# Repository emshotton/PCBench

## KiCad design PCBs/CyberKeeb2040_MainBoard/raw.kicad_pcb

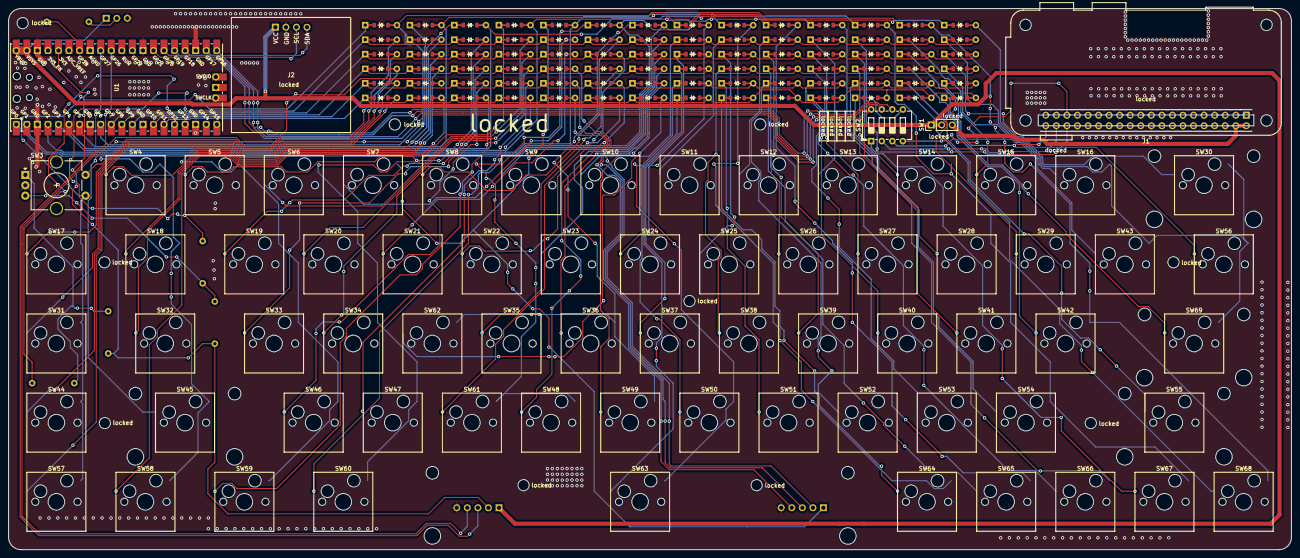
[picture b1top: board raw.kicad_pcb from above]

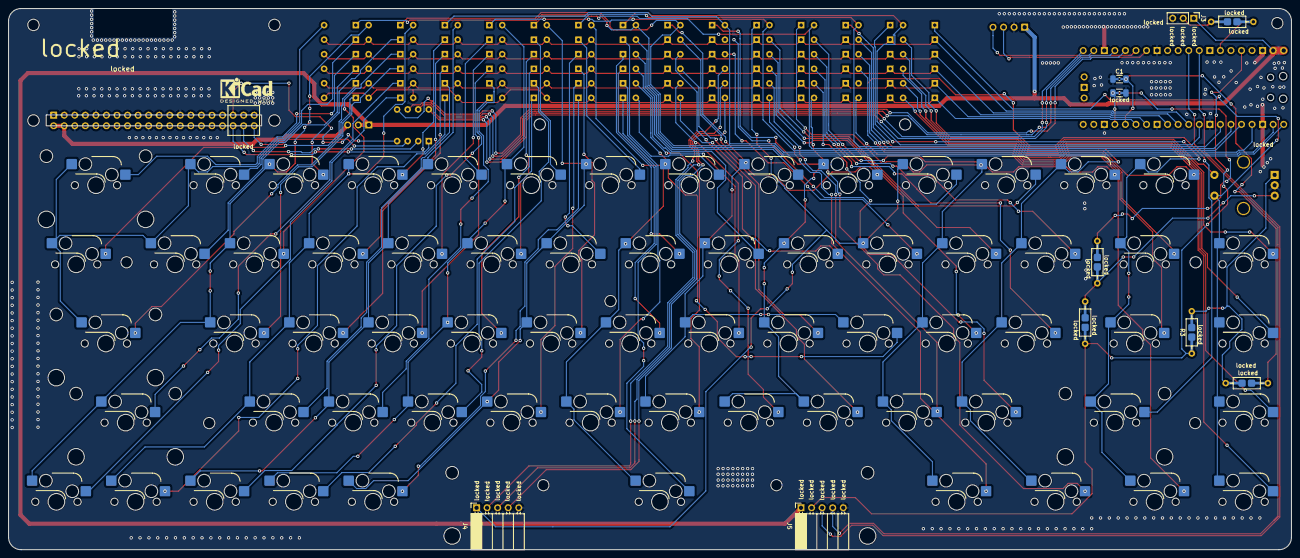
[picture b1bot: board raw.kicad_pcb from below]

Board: 2 copper layers, 308.8 x 130.2 mm, 166 parts (76 on the bottom side), 118 nets.

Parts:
C1: 0.01 μF; C_1206_3216Metric_Pad1.33x1.80mm_HandSolder
D1, D2, D3, D4, D5, D6, D7, D8, D9, D10, D11, D12, D13, D14, D15, D16, D17, D18, D19, D20, D21, D22, D23, D24, D25, D26, D27, D28, D29, D30, D31, D32, D33, D34, D35, D36, D37, D38, D39, D40, D41, D42, D43, D44, D45, D46, D47, D48, D49, D50, D51, D52, D53, D54, D55, D56, D57, D58, D59, D60, D61, D62, D63, D64, D65, D66, D67, D68, D69, D70, D71, D72, D73, D74, D75, D76, D77, D78, D79, D80, D81, D82, D83, D84: D; D_DO-35_SOD27_P7.62mm_Horizontal
J1: Pi_Zero; Raspberry_Pi_Zero_Socketed_THT_MountingHoles_Castellated
J2: JMD0.96C
J3: WS2812; PinHeader_1x03_P2.54mm_Vertical
J4: Extra_Keys; PinSocket_1x05_P2.54mm_Horizontal
J5: JoyStick_Or_I2C1; PinSocket_1x05_P2.54mm_Horizontal
R1: 330; R_Axial_DIN0207_L6.3mm_D2.5mm_P10.16mm_Horizontal_0603
R2, R3, R4, R5: 10k; R_Axial_DIN0207_L6.3mm_D2.5mm_P10.16mm_Horizontal_0402
SW1: PiPowerSwitch; PinHeader_1x03_P2.54mm_Vertical
SW2: SPI_SW; SW_DIP_SPSTx04_Slide_6.7x11.72mm_W7.62mm_P2.54mm_LowProfile
SW3: RotaryEncoder_Switch; RotaryEncoder_Alps_EC11E-Switch_Vertical_H20mm_CircularMoun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
SW4: SW_`; SW_Hotswap_Kailh_MX_1.00u
SW5: SW_1; SW_Hotswap_Kailh_MX_1.00u
SW6: SW_2; SW_Hotswap_Kailh_MX_1.00u
SW7: SW_3; SW_Hotswap_Kailh_MX_1.00u
SW8: SW_4; SW_Hotswap_Kailh_MX_1.00u
SW9: SW_5; SW_Hotswap_Kailh_MX_1.00u
SW10: SW_6; SW_Hotswap_Kailh_MX_1.00u
SW11: SW_7; SW_Hotswap_Kailh_MX_1.00u
SW12: SW_8; SW_Hotswap_Kailh_MX_1.00u
SW13: SW_9; SW_Hotswap_Kailh_MX_1.00u
SW14: SW_0; SW_Hotswap_Kailh_MX_1.00u
SW15: SW_-; SW_Hotswap_Kailh_MX_1.00u
SW16: SW_+; SW_Hotswap_Kailh_MX_1.00u
SW17: SW_esc; SW_Hotswap_Kailh_MX_1.00u
SW18: SW_tab; SW_Hotswap_Kailh_MX_1.50u
SW19: SW_q; SW_Hotswap_Kailh_MX_1.00u
SW20: SW_w; SW_Hotswap_Kailh_MX_1.00u
SW21: SW_e; SW_Hotswap_Kailh_MX_1.00u
SW22: SW_r; SW_Hotswap_Kailh_MX_1.00u
SW23: SW_t; SW_Hotswap_Kailh_MX_1.00u
SW24: SW_y; SW_Hotswap_Kailh_MX_1.00u
SW25: SW_u; SW_Hotswap_Kailh_MX_1.00u
SW26: SW_i; SW_Hotswap_Kailh_MX_1.00u
SW27: SW_o; SW_Hotswap_Kailh_MX_1.00u
SW28: SW_p; SW_Hotswap_Kailh_MX_1.00u
SW29: SW_[; SW_Hotswap_Kailh_MX_1.00u
SW30: SW_back; SW_Hotswap_Kailh_MX_2.00u
SW31: SW_del; SW_Hotswap_Kailh_MX_1.00u
SW32: SW_caps; SW_Hotswap_Kailh_MX_1.75u
SW33: SW_a; SW_Hotswap_Kailh_MX_1.00u
SW34: SW_s; SW_Hotswap_Kailh_MX_1.00u
SW35: SW_f; SW_Hotswap_Kailh_MX_1.00u
SW36: SW_g; SW_Hotswap_Kailh_MX_1.00u
SW37: SW_h; SW_Hotswap_Kailh_MX_1.00u
SW38: SW_j; SW_Hotswap_Kailh_MX_1.00u
SW39: SW_k; SW_Hotswap_Kailh_MX_1.00u
SW40: SW_l; SW_Hotswap_Kailh_MX_1.00u
SW41: SW_;; SW_Hotswap_Kailh_MX_1.00u
SW42: SW_'; SW_Hotswap_Kailh_MX_1.00u
SW43: SW_]; SW_Hotswap_Kailh_MX_1.00u
SW44: SW_ins; SW_Hotswap_Kailh_MX_1.00u
SW45: SW_shift; SW_Hotswap_Kailh_MX_2.25u
SW46: SW_z; SW_Hotswap_Kailh_MX_1.00u
SW47: SW_x; SW_Hotswap_Kailh_MX_1.00u
SW48: SW_v; SW_Hotswap_Kailh_MX_1.00u
SW49: SW_b; SW_Hotswap_Kailh_MX_1.00u
SW50: SW_n; SW_Hotswap_Kailh_MX_1.00u
SW51: SW_m; SW_Hotswap_Kailh_MX_1.00u
SW52: SW_,; SW_Hotswap_Kailh_MX_1.00u
SW53: SW_.; SW_Hotswap_Kailh_MX_1.00u
SW54: SW_/; SW_Hotswap_Kailh_MX_1.00u
SW55: SW_r_shift; SW_Hotswap_Kailh_MX_2.75u
SW56: SW_bkslash; SW_Hotswap_Kailh_MX_1.50u
SW57: SW_fn1; SW_Hotswap_Kailh_MX_1.00u
SW58: SW_ctrl; SW_Hotswap_Kailh_MX_1.25u
SW59: SW_super; SW_Hotswap_Kailh_MX_1.25u
SW60: SW_alt; SW_Hotswap_Kailh_MX_1.25u
SW61: SW_c; SW_Hotswap_Kailh_MX_1.00u
SW62: SW_d; SW_Hotswap_Kailh_MX_1.00u
SW63: SW_space; SW_Hotswap_Kailh_MX_6.25u
SW64: SW_fn2; SW_Hotswap_Kailh_MX_1.00u
SW65: SW_left; SW_Hotswap_Kailh_MX_1.00u
SW66: SW_down; SW_Hotswap_Kailh_MX_1.00u
SW67: SW_up; SW_Hotswap_Kailh_MX_1.00u
SW68: SW_right; SW_Hotswap_Kailh_MX_1.00u
SW69: SW_enter; SW_Hotswap_Kailh_MX_2.25u
U1: Pico; RPi_Pico_SMD_TH
locked: 0.01 μF; C_1206_3216Metric_Pad1.33x1.80mm_HandSolder

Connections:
+3V3: J5.2, R3.2, R4.1, U1.36 (3V3)
+5V: J2.1, J3.1, J5.1, SW1.1 (A), SW1.2 (B), U1.39 (VSYS), U1.40 (VBUS)
/Pi_VCC: J1.2, J1.4, SW1.3 (C)
ANG1: J5.3, U1.32 (GPIO27_ADC1)
ANG2: J5.4, U1.31 (GPIO26_ADC0)
C0: D1.2 (A), D8.1 (K), U1.9 (GPIO6)
C1: D2.2 (A), D9.1 (K), U1.7 (GPIO5)
C2: D3.2 (A), D10.1 (K), U1.6 (GPIO4)
C3: D4.2 (A), D11.1 (K), U1.5 (GPIO3)
C4: D5.2 (A), D12.1 (K), U1.4 (GPIO2)
C5: D6.2 (A), D13.1 (K), U1.2 (GPIO1)
C6: D7.2 (A), D14.1 (K), U1.1 (GPIO0)
Enc1: C1.2, R2.1, U1.16 (GPIO12)
Enc2: R5.2, U1.17 (GPIO13), locked.1
Encoder_SW_1: D15.2 (A), SW3.S2
Encoder_SW_2: D1.1 (K), SW3.S1, SW17.2 (B), SW31.2 (B), SW44.2 (B), SW57.2 (B)
Extra1: D47.2 (A), J4.2
Extra2: D61.2 (A), J4.3
Extra3: D75.2 (A), J4.4
ExtraSource: D5.1 (K), J4.1, SW7.2 (B), SW21.2 (B)
GND: C1.1, J1.6, J1.9, J1.14, J1.20, J1.25, J1.30, J1.34, J2.2, J3.3, J4.5, J5.5, SW3.C, U1.3 (GND), U1.8 (GND), U1.13 (GND), U1.18 (GND), U1.23 (GND), U1.28 (GND), U1.38 (GND), locked.2
I2C0_SCL: J2.3, U1.27 (GPIO21)
I2C0_SDA: J2.4, U1.26 (GPIO20)
LED: R1.1, U1.34 (GPIO28_ADC2)
unnamed: D2.1 (K), SW4.2 (B), SW18.2 (B), SW32.2 (B), SW45.2 (B), SW58.2 (B)
unnamed: D3.1 (K), SW5.2 (B), SW19.2 (B), SW33.2 (B), SW46.2 (B), SW59.2 (B)
unnamed: D4.1 (K), SW6.2 (B), SW20.2 (B), SW34.2 (B), SW47.2 (B), SW60.2 (B)
unnamed: D6.1 (K), SW8.2 (B), SW22.2 (B), SW35.2 (B), SW48.2 (B), SW61.2 (B)
unnamed: D7.1 (K), SW9.2 (B), SW23.2 (B), SW36.2 (B), SW49.2 (B), SW62.2 (B)
unnamed: D8.2 (A), SW10.2 (B), SW24.2 (B), SW37.2 (B), SW50.2 (B), SW63.2 (B)
unnamed: D9.2 (A), SW11.2 (B), SW25.2 (B), SW38.2 (B), SW51.2 (B), SW64.2 (B)
unnamed: D10.2 (A), SW12.2 (B), SW26.2 (B), SW39.2 (B), SW52.2 (B), SW65.2 (B)
unnamed: D11.2 (A), SW13.2 (B), SW27.2 (B), SW40.2 (B), SW53.2 (B), SW66.2 (B)
unnamed: D12.2 (A), SW14.2 (B), SW28.2 (B), SW41.2 (B), SW54.2 (B), SW67.2 (B)
unnamed: D13.2 (A), SW15.2 (B), SW29.2 (B), SW42.2 (B), SW55.2 (B), SW68.2 (B)
unnamed: D14.2 (A), SW16.2 (B), SW30.2 (B), SW43.2 (B), SW56.2 (B), SW69.2 (B)
unnamed: D16.2 (A), SW4.1 (A)
unnamed: D17.2 (A), SW5.1 (A)
unnamed: D18.2 (A), SW6.1 (A)
unnamed: D19.2 (A), SW7.1 (A)
unnamed: D20.2 (A), SW8.1 (A)
unnamed: D21.2 (A), SW9.1 (A)
unnamed: D22.1 (K), SW10.1 (A)
unnamed: D23.1 (K), SW11.1 (A)
unnamed: D24.1 (K), SW12.1 (A)
unnamed: D25.1 (K), SW13.1 (A)
unnamed: D26.1 (K), SW14.1 (A)
unnamed: D27.1 (K), SW15.1 (A)
unnamed: D28.1 (K), SW16.1 (A)
unnamed: D29.2 (A), SW17.1 (A)
unnamed: D30.2 (A), SW18.1 (A)
unnamed: D31.2 (A), SW19.1 (A)
unnamed: D32.2 (A), SW20.1 (A)
unnamed: D33.2 (A), SW21.1 (A)
unnamed: D34.2 (A), SW22.1 (A)
unnamed: D35.2 (A), SW23.1 (A)
unnamed: D36.1 (K), SW24.1 (A)
unnamed: D37.1 (K), SW25.1 (A)
unnamed: D38.1 (K), SW26.1 (A)
unnamed: D39.1 (K), SW27.1 (A)
unnamed: D40.1 (K), SW28.1 (A)
unnamed: D41.1 (K), SW29.1 (A)
unnamed: D42.1 (K), SW30.1 (A)
unnamed: D43.2 (A), SW31.1 (A)
unnamed: D44.2 (A), SW32.1 (A)
unnamed: D45.2 (A), SW33.1 (A)
unnamed: D46.2 (A), SW34.1 (A)
unnamed: D48.2 (A), SW35.1 (A)
unnamed: D49.2 (A), SW36.1 (A)
unnamed: D50.1 (K), SW37.1 (A)
unnamed: D51.1 (K), SW38.1 (A)
unnamed: D52.1 (K), SW39.1 (A)
unnamed: D53.1 (K), SW40.1 (A)
unnamed: D54.1 (K), SW41.1 (A)
unnamed: D55.1 (K), SW42.1 (A)
unnamed: D56.1 (K), SW43.1 (A)
unnamed: D57.2 (A), SW44.1 (A)
unnamed: D58.2 (A), SW45.1 (A)
unnamed: D59.2 (A), SW46.1 (A)
unnamed: D60.2 (A), SW47.1 (A)
unnamed: D62.2 (A), SW48.1 (A)
unnamed: D63.2 (A), SW49.1 (A)
unnamed: D64.1 (K), SW50.1 (A)
unnamed: D65.1 (K), SW51.1 (A)
unnamed: D66.1 (K), SW52.1 (A)
unnamed: D67.1 (K), SW53.1 (A)
unnamed: D68.1 (K), SW54.1 (A)
unnamed: D69.1 (K), SW55.1 (A)
unnamed: D70.1 (K), SW56.1 (A)
unnamed: D71.2 (A), SW57.1 (A)
unnamed: D72.2 (A), SW58.1 (A)
unnamed: D73.2 (A), SW59.1 (A)
unnamed: D74.2 (A), SW60.1 (A)
unnamed: D76.2 (A), SW61.1 (A)
unnamed: D77.2 (A), SW62.1 (A)
unnamed: D78.1 (K), SW63.1 (A)
unnamed: D79.1 (K), SW64.1 (A)
unnamed: D80.1 (K), SW65.1 (A)
unnamed: D81.1 (K), SW66.1 (A)
unnamed: D82.1 (K), SW67.1 (A)
unnamed: D83.1 (K), SW68.1 (A)
unnamed: D84.1 (K), SW69.1 (A)
unnamed: J3.2, R1.2
unnamed: R2.2, R3.1, SW3.A
unnamed: R4.2, R5.1, SW3.B
PI_SPI_CS: J1.36, SW2.1
PI_SPI_MISO: J1.35, SW2.4
PI_SPI_MOSI: J1.38, SW2.2
PI_SPI_SCK: J1.40, SW2.3
R0: D15.1 (K), D16.1 (K), D17.1 (K), D18.1 (K), D19.1 (K), D20.1 (K), D21.1 (K), D22.2 (A), D23.2 (A), D24.2 (A), D25.2 (A), D26.2 (A), D27.2 (A), D28.2 (A), U1.10 (GPIO7)
R1: D29.1 (K), D30.1 (K), D31.1 (K), D32.1 (K), D33.1 (K), D34.1 (K), D35.1 (K), D36.2 (A), D37.2 (A), D38.2 (A), D39.2 (A), D40.2 (A), D41.2 (A), D42.2 (A), U1.11 (GPIO8)
R2: D43.1 (K), D44.1 (K), D45.1 (K), D46.1 (K), D47.1 (K), D48.1 (K), D49.1 (K), D50.2 (A), D51.2 (A), D52.2 (A), D53.2 (A), D54.2 (A), D55.2 (A), D56.2 (A), U1.12 (GPIO9)
R3: D57.1 (K), D58.1 (K), D59.1 (K), D60.1 (K), D61.1 (K), D62.1 (K), D63.1 (K), D64.2 (A), D65.2 (A), D66.2 (A), D67.2 (A), D68.2 (A), D69.2 (A), D70.2 (A), U1.14 (GPIO10)
R4: D71.1 (K), D72.1 (K), D73.1 (K), D74.1 (K), D75.1 (K), D76.1 (K), D77.1 (K), D78.2 (A), D79.2 (A), D80.2 (A), D81.2 (A), D82.2 (A), D83.2 (A), D84.2 (A), U1.15 (GPIO11)
SPI_CS: SW2.8, U1.22 (GPIO17)
SPI_MISO: SW2.5, U1.25 (GPIO19)
SPI_MOSI: SW2.7, U1.21 (GPIO16)
SPI_SCK: SW2.6, U1.24 (GPIO18)

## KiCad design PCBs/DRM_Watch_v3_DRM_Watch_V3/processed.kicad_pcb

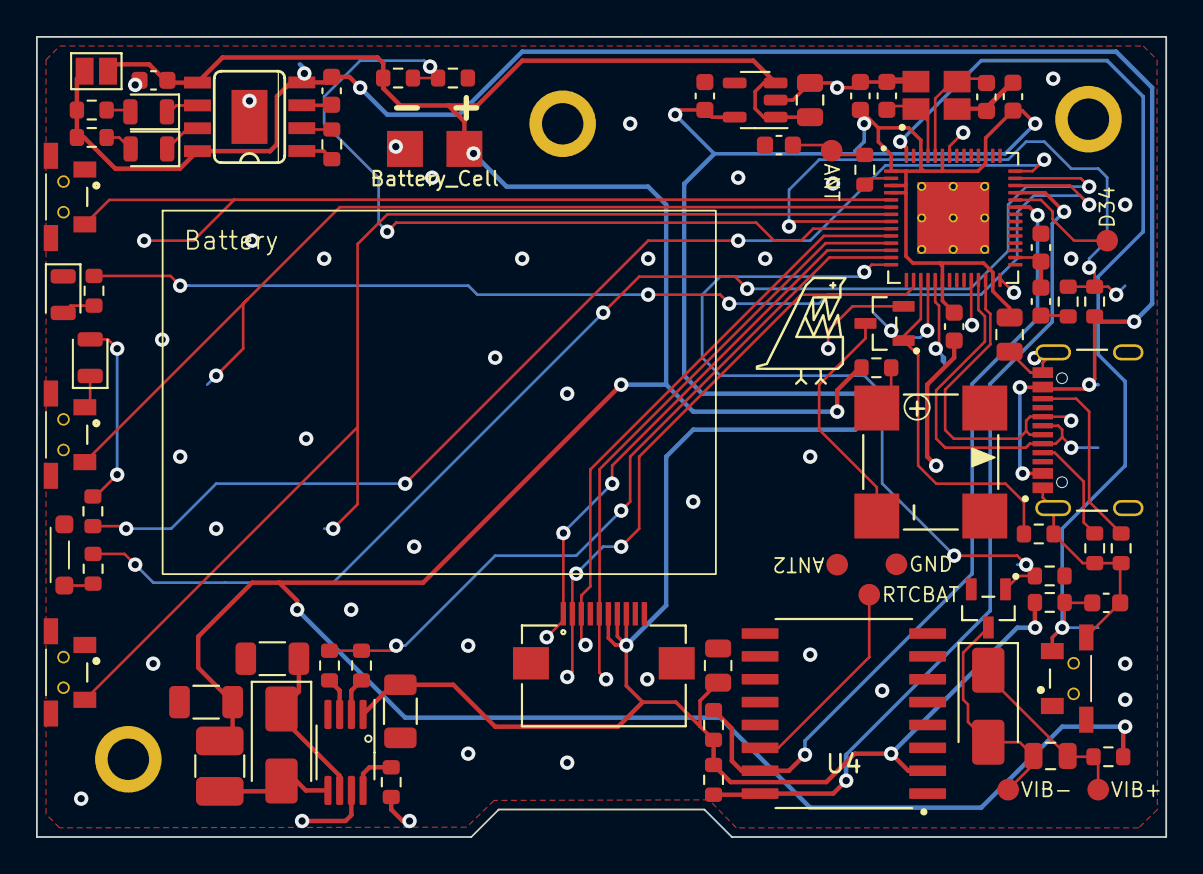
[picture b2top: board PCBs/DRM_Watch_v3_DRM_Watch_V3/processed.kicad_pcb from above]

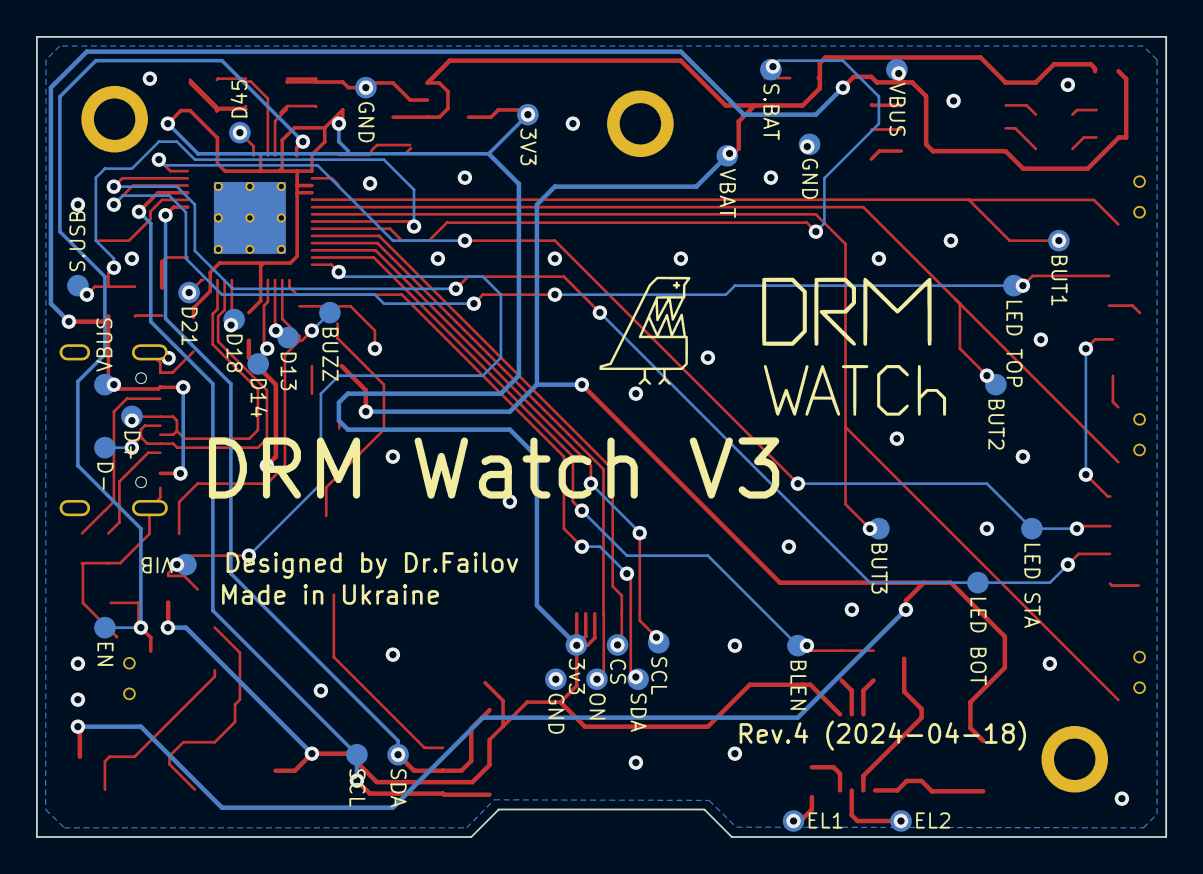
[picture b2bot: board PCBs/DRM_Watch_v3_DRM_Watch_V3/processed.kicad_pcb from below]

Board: 2 copper layers, 62.7 x 44.4 mm, 112 parts (35 on the bottom side), 57 nets.

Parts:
BT1: Battery_Cell; Battery
C1: 0.1uF; C_0805_2012Metric
C2, C3, C13: 10pF; C_0603_1608Metric
C4, C5, C6, C8: 0.1uF; C_0603_1608Metric
C7, C14: 1uF; C_0603_1608Metric
C9, C10, C19: 1uF; C_0805_2012Metric
C11, C12, C15: 10uF; C_0603_1608Metric
C16: 12nF 200V; C_1206
C17: 4.7uF; C_1206
C18: 0.1uF; C_1206
D1, D4: LED RED; HOLE_LED_0805_2012Metric
D2: 020 SMD Side View LED White 6000K; SMD-LED-Side-View
D3, D5: LED BLUE; HOLE_LED_0805_2012Metric
D6, D7: US1D
J1: TYPE-C-31-M-12; HRO_TYPE-C-31-M-12
J2: FPC 10pin 0.5mm pitch; 687110149022
JP1: Connect this to directly power VCC from USB; SolderJumper-2_P1.3mm_Open_Pad1.0x1.5mm
L1: 220uH; Inductor-L_1210_3225Metric
LS1: CMT-7525S-SMT; CUI_CMT-7525S-SMT
M1, M2, M3: Brass SMTSO-M1.4X3X1.5-2X0.8; m1.4-screw-mount
Q1, Q2: 2N7002LT1G (SOT-23-3); SOT95P240X111-3N
R1, R7, R8, R22: 1K; R_0603_1608Metric
R2, R3: 5.1K; R_0603_1608Metric
R4, R5, R6, R10, R23: R22; R_0603_1608Metric
R9: 2K; R_0603_1608Metric
R11, R12, R13, R14: 100K; R_0603_1608Metric
R15: 0 ohm; R_0603_1608Metric
R16: 10K; R_0603_1608Metric
R17: 560K; R_0603_1608Metric
R18: 2M; R_0603_1608Metric
R19, R20: 4.3K; R_0603_1608Metric
R21: 500R; R_0603_1608Metric
S1, S2, S3, S4: 2*4*3.5mm Micro SMD Tact Switch Side Button; SW_TL3330AF130QG
TP1: 3V3; TestPoint_Pad
TP2: VBAT; TestPoint_Pad
TP3: BUT1; TestPoint_Pad
TP4: BUT2; TestPoint_Pad
TP5: BUT3; TestPoint_Pad
TP6, TP8, TP9, TP17: GND; TestPoint_Pad
TP7, TP23: VBUS; TestPoint_Pad
TP10: EN; TestPoint_Pad
TP11: S.BAT; TestPoint_Pad
TP12: S.USB; TestPoint_Pad
TP13, TP30: SCL; TestPoint_Pad
TP14, TP29: SDA; TestPoint_Pad
TP15: CS; TestPoint_Pad
TP16: ON; TestPoint_Pad
TP18: 3v3; TestPoint_Pad
TP19: LED TOP; TestPoint_Pad
TP20: LED BOT; TestPoint_Pad
TP21: LED STA; TestPoint_Pad
TP22: BUZZ; TestPoint_Pad
TP24: D+; TestPoint_Pad
TP25: D-; TestPoint_Pad
TP26: EL1; TestPoint_Pad
TP27: ANT; TestPoint_Pad
TP28: ANT2; TestPoint_Pad
TP31: D14; TestPoint_Pad
TP32: EL2; TestPoint_Pad
TP33: D18; TestPoint_Pad
TP34: D21; TestPoint_Pad
TP35: D45; TestPoint_Pad
TP36: D34; TestPoint_Pad
TP37: D13; TestPoint_Pad
TP38: BLEN; TestPoint_Pad
TP39: RTCBAT; TestPoint_Pad
TP40: VIB+; TestPoint_Pad
TP41: VIB-; TestPoint_Pad
TP42: VIB; TestPoint_Pad
U1: ESP32-S2FN4R2; QFN-56-1EP_7x7mm_P0.4mm_EP4x4mm_ThermalVias
U2: ME6211 SOT23-5 3.3V; ME6211 SOT-23-5
U3: TP4056; SO08
U4: DS3231S; SOIC127P1032X265-16N
U5: Microchip HV857; HV857
Y1: 3225 4PIN 40Mhz 3.2*2.5mm Passive SMD Quartz Reso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; Oscilator

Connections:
+3V3: C1.2, C4.1, C5.1, C6.1, C10.1, C15.2, C18.1, J2.6 (VDDA), J2.7 (VDD), J2.8 (EXTMODE), R16.1, R19.2, R20.2, TP1.1, TP18.1, U1.1 (VDDA), U1.3 (VDD3P3), U1.4 (VDD3P3), U1.20 (VDD3P3_RTC), U1.27 (VDD3P3_RTC_IO), U1.45 (VDD3P3_CPU), U1.51 (VDDA), U1.54 (VDDA), U2.5 (V_out), U4.2 (VCC), U5.1 (VDD)
GND: BT1.2 (-), C1.1, C2.1, C3.2, C4.2, C5.2, C6.2, C7.2, C8.2, C9.2, C10.2, C11.2, C12.1, C13.1, C14.1, C15.1, C16.2, C17.2, C18.2, D1.1 (K), D2.1 (K), D5.1 (K), J1.A1_B12 (GND), J1.B1_A12 (GND), J1.S1 (SHIELD), J1.S2 (SHIELD), J1.S3 (SHIELD), J1.S4 (SHIELD), J2.9 (GND), J2.10 (GNDA), J2.Z1 (Mount), J2.Z2 (Mount), M1.1, M2.1, M3.1, Q1.2, Q2.2, R1.2, R2.2, R3.1, R9.2, R12.2, R14.2, R22.2, S1.1, S1.3 (Shield), S2.1, S2.3 (Shield), S3.1, S3.3 (Shield), S4.1, S4.3 (Shield), TP6.1, TP8.1, TP9.1, TP17.1, U1.57 (GND), U2.2 (GND), U3.1 (TEMP), U3.3 (GND), U3.9 (HEAT), U4.5 (N.C.), U4.6 (N.C.), U4.7 (N.C.), U4.8 (N.C.), U4.9 (N.C.), U4.10 (N.C.), U4.11 (N.C.), U4.12 (N.C.), U4.13 (GND), U5.4 (GND), Y1.2 (GND), Y1.4 (GND)
unnamed: C13.2, R15.1, TP27.1
unnamed: D1.2 (A), R5.1
unnamed: D2.2 (A), R6.1
unnamed: D3.2 (A), R7.2
unnamed: D3.1 (K), U3.6 (STDBY)
unnamed: D4.2 (A), R8.2
unnamed: D4.1 (K), U3.7 (CHRGE)
unnamed: D5.2 (A), R10.1
unnamed: D6.2 (A), L1.1, U5.5 (LX)
unnamed: C16.1, D6.1 (K), U5.6 (CS)
unnamed: C19.1, D7.2 (A), Q2.3, TP41.1
unnamed: C19.2, D7.1 (K), R23.1, TP40.1
unnamed: J1.A5 (CC1), R3.2
unnamed: J1.B5 (CC2), R2.1
unnamed: J1.A7 (DN1), J1.B7 (DN2), TP25.1, U1.25 (GPIO19/ADC2_CH8/USB_D-)
unnamed: J1.A6 (DP1), J1.B6 (DP2), TP24.1, U1.26 (GPIO20/ADC2_CH9/USB_D+)
unnamed: J2.3 (CS), TP15.1, U1.10 (GPIO5/ADC1_CH4)
unnamed: J2.5 (ON\OFF), TP16.1, U1.11 (GPIO6/ADC1_CH5)
unnamed: J2.1 (SCL), TP13.1, U1.12 (GPIO7/ADC1_CH6)
unnamed: J2.2 (SDA), TP14.1, U1.16 (GPIO11/ADC2_CH0)
unnamed: LS1.N, Q1.3
unnamed: LS1.P, R4.1
unnamed: R21.1, TP26.1
unnamed: C14.2, R16.2, S3.2, TP10.1, U1.56 (CHIP_PU/RESET)
unnamed: S1.2, TP3.1, U1.5 (GPIO0/BOOT)
unnamed: S2.2, TP4.1, U1.6 (GPIO1/ADC1_CH0)
unnamed: S4.2, TP5.1, U1.7 (GPIO2/ADC1_CH1)
unnamed: R13.2, R14.1, TP12.1, U1.8 (GPIO3/ADC1_CH2)
unnamed: R11.2, R12.1, TP11.1, U1.9 (GPIO4/ADC1_CH3)
unnamed: R17.1, R18.1, TP38.1, U1.13 (GPIO8/ADC1_CH7)
unnamed: Q2.1, R22.1, TP42.1, U1.14 (GPIO9/ADC1_CH8)
unnamed: Q1.1, R1.1, TP22.1, U1.17 (GPIO12/ADC2_CH1)
unnamed: TP37.1, U1.18 (GPIO13/ADC2_CH2)
unnamed: TP31.1, U1.19 (GPIO14/ADC2_CH3)
unnamed: TP33.1, U1.24 (GPIO18/ADC2_CH7/DAC_2)
unnamed: TP34.1, U1.28 (GPIO21)
unnamed: R19.1, TP29.1, U1.37 (GPIO33), U4.15 (SDA)
unnamed: TP36.1, U1.38 (GPIO34)
unnamed: R20.1, TP30.1, U1.39 (GPIO35), U4.16 (SCL)
unnamed: R5.2, TP19.1, U1.40 (GPIO36)
unnamed: R6.2, TP20.1, U1.41 (GPIO37)
unnamed: R10.2, TP21.1, U1.42 (GPIO38)
unnamed: TP35.1, U1.50 (GPIO45)
unnamed: R15.2, U1.2 (LNA_IN/RF)
unnamed: C7.1, C8.1, U1.30 (VDD_SPI)
unnamed: C3.1, U1.52 (XTAL_N), Y1.3 (XTAL_N)
unnamed: C2.2, U1.53 (XTAL_P), Y1.1 (XTAL_P)
unnamed: R9.1, U3.2 (PROG)
unnamed: TP39.1, U4.14 (VBAT)
unnamed: R18.2, U5.3 (REL-Osc)
unnamed: R17.2, U5.2 (RSW-Osc)
unnamed: R21.2, U5.8 (VA)
unnamed: TP32.1, U5.7 (VB)
VBUS: C12.2, J1.A4_B9 (VBUS), J1.B4_A9 (VBUS), JP1.1 (A), R7.1, R8.1, R13.1, TP7.1, TP23.1, U3.4 (VCC), U3.8 (CE)
VCC: BT1.1 (+), C9.1, C11.1, C17.1, JP1.2 (B), L1.2, R4.2, R11.1, R23.2, TP2.1, U2.1 (V_in), U2.3 (CE), U3.5 (BAT)

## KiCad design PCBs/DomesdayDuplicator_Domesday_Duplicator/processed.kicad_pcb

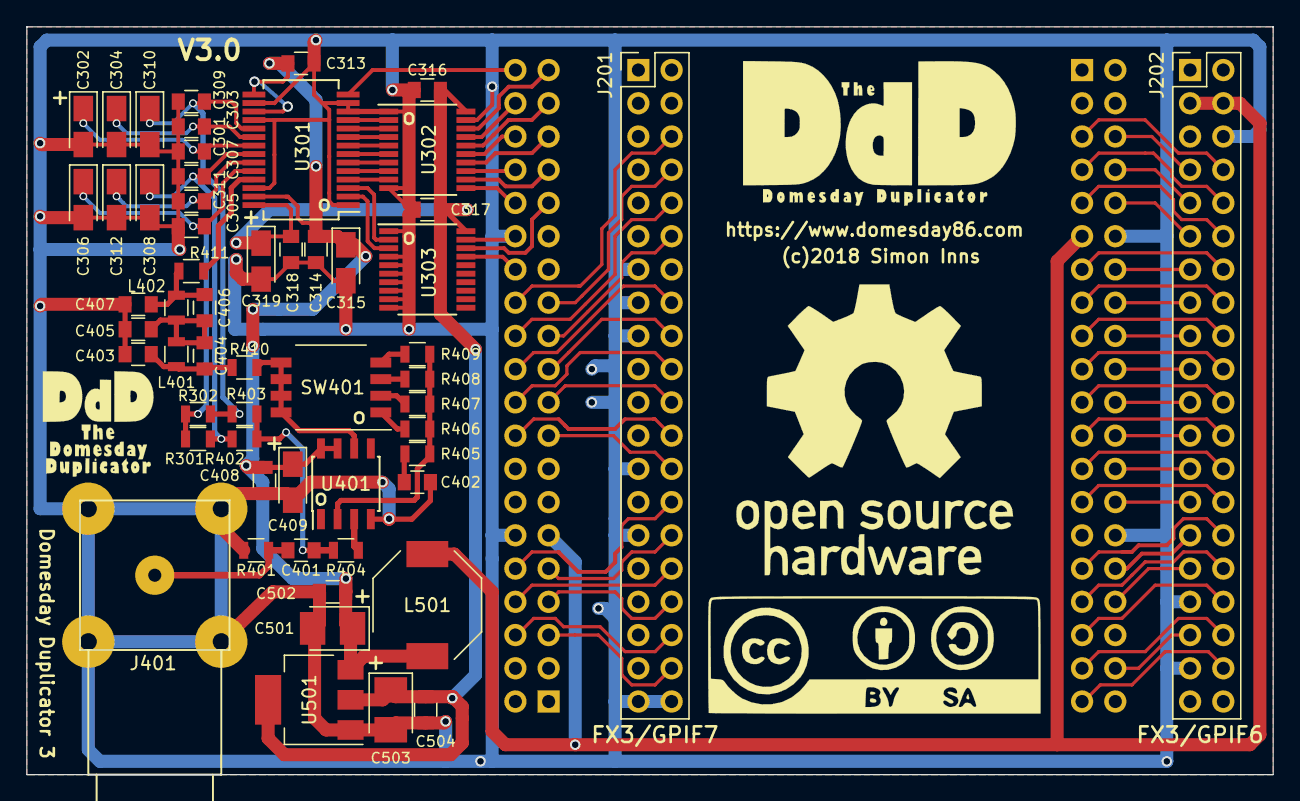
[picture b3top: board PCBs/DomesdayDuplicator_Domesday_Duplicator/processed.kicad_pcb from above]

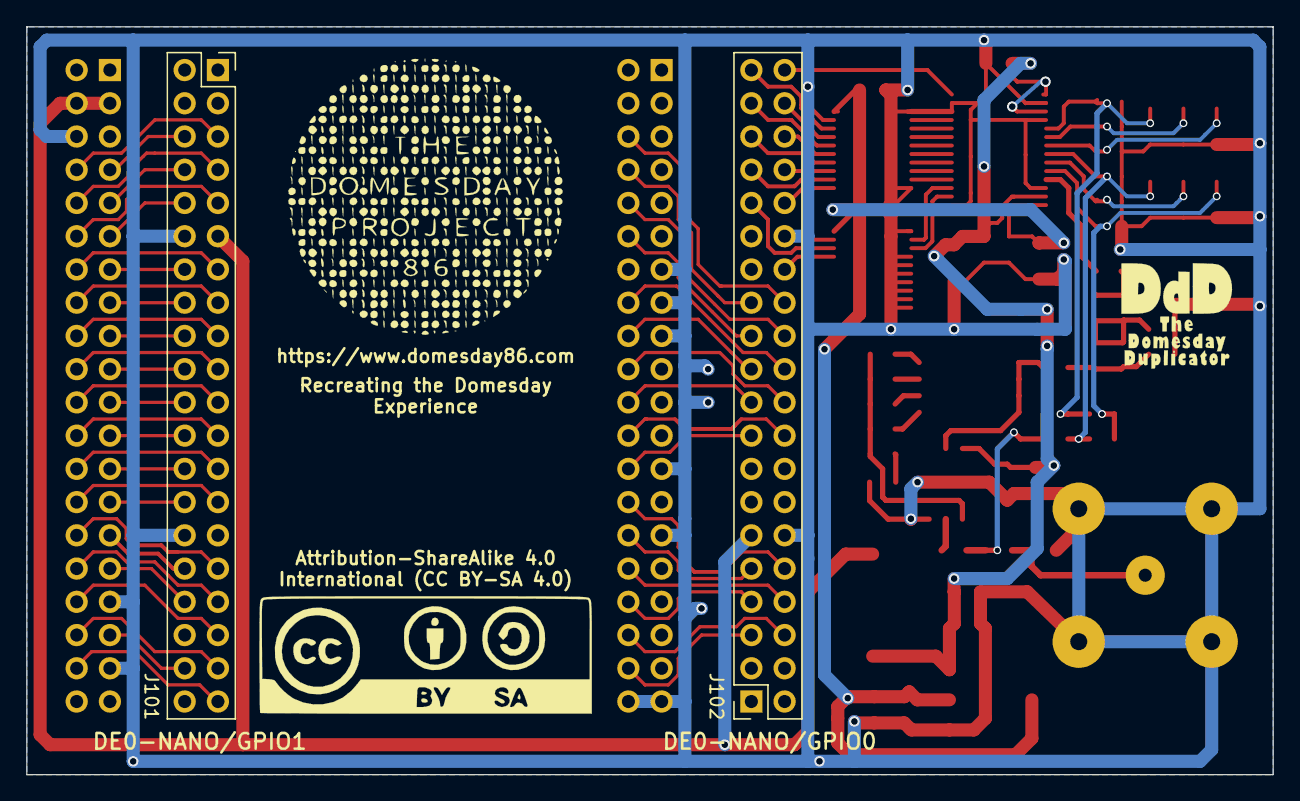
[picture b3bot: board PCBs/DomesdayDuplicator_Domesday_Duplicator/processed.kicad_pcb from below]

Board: 2 copper layers, 95.2 x 57.2 mm, 59 parts (2 on the bottom side), 91 nets.

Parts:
C301, C303, C305, C307, C309, C311, C313, C314, C316, C317, C318, C401, C402, C408, C502, C504: 100nF; C_0805
C302, C304, C306, C308, C310, C312, C315, C319, C409: 2.2uF Tant; CP_Tantalum_Case-A_EIA-3216-18_Reflow
C403: 330pF; C_0805
C404: 33pF; C_0805
C405: 470pF; C_0805
C406: 100pF; C_0805
C407: 270pF; C_0805
C501, C503: 10uF TANT; CP_Tantalum_Case-B_EIA-3528-21_Reflow
J101: DE0-Nano_GPIO1; Socket_Strip_Straight_2x20_Pitch2.54mm
J102: DE0-Nano_GPIO0; Socket_Strip_Straight_2x20_Pitch2.54mm
J201: GPIFII_J7; Pin_Header_Straight_2x20_Pitch2.54mm
J202: GPIFII_J6; Pin_Header_Straight_2x20_Pitch2.54mm
J401: BNC_Rosenberger; BNC Socket
L401: 680nH; L_0805
L402: 560nH; L_0805
L501: 100uH; Inductor_Bourns-SRU8043
R301, R402, R403, R407: 1K; R_0805
R302: 1K2; R_0805
R401: 56R; R_0805
R404: 100R; R_0805
R405: 200R; R_0805
R406: 1K5; R_0805
R408: 680R; R_0805
R409: 560R; R_0805
R410, R411: 47R; R_0805
SW401: Gain Select; SW_DIP_x4_W7.62mm_Slide_Copal_CHS-B
U301: ADS825; SSOP-28_5.3x10.2mm_Pitch0.65mm
U302, U303: 74LVTH541_PWR; TSSOP-20_4.4x6.5mm_Pitch0.65mm
U401: OPA690; SOIC-8_3.9x4.9mm_Pitch1.27mm
U501: LM1117-3.3; SOT-223-3_TabPin2

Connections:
+3.3VA: C316.1, C317.1, C318.1, C319.1, C503.1, C504.1, U301.28, U302.20, U303.20, U501.2
+5V: J101.11, J102.11, J202.3, J202.4, L501.2
+5VA: C313.1, C314.1, C315.1, C408.1, C409.1, C501.1, C502.1, L501.1, U301.15, U301.17, U301.27, U401.7, U401.8, U501.3
/ADC/IN: R411.2, U301.25
/ADC/REFB: C309.1, C310.1, R302.1, R403.1, U301.19
/ADC/REFT: C307.1, C308.1, R301.2, R402.2, U301.22
ADC_CLK: J102.40, U301.14
ADC_DATA0: J102.39, U302.18
ADC_DATA1: J102.38, U302.17
ADC_DATA2: J102.37, U302.16
ADC_DATA3: J102.36, U302.15
ADC_DATA4: J102.35, U302.14
ADC_DATA5: J102.34, U302.13
ADC_DATA6: J102.33, U302.12
ADC_DATA7: J102.32, U302.11
ADC_DATA8: J102.31, U303.18
ADC_DATA9: J102.28, U303.17
GND: C301.2, C302.2, C303.2, C304.2, C305.2, C306.2, C307.2, C308.2, C309.2, C310.2, C311.2, C312.2, C313.2, C314.2, C315.2, C316.2, C317.2, C318.2, C319.2, C402.2, C403.2, C405.2, C407.2, C408.2, C409.2, C501.2, C502.2, C503.2, C504.2, J101.12, J101.30, J102.12, J102.30, J201.13, J201.15, J201.17, J201.25, J201.29, J201.39, J201.40, J202.6, J202.33, J202.37, J401.2, J401.3, J401.4, J401.5, R401.1, U301.1, U301.12, U301.13, U301.16, U301.18, U301.26, U302.1, U302.10, U302.19, U303.1, U303.4, U303.5, U303.6, U303.7, U303.8, U303.9, U303.10, U303.19, U401.4, U501.1
unnamed: C301.1, C302.1, U301.21
unnamed: C303.1, C304.1, U301.20
unnamed: C305.1, C306.1, R301.1, R302.2, U301.24
unnamed: C311.1, C312.1, U301.23
unnamed: C401.1, R402.1, R403.2, R404.1
unnamed: C401.2, J401.1, R401.2
unnamed: C402.1, R405.1
unnamed: C403.1, C404.1, L401.2, R410.2
unnamed: C404.2, C405.1, C406.1, L401.1, L402.2
unnamed: C406.2, C407.1, L402.1, R411.1
unnamed: R404.2, U401.3
unnamed: R405.2, R406.1, R407.1, R408.1, R409.1, U401.2
unnamed: R406.2, SW401.1
unnamed: R407.2, SW401.2
unnamed: R408.2, SW401.3
unnamed: R409.2, SW401.4
unnamed: R410.1, SW401.5, SW401.6, SW401.7, SW401.8, U401.6
unnamed: U301.2, U303.3
unnamed: U301.3, U303.2
unnamed: U301.4, U302.9
unnamed: U301.5, U302.8
unnamed: U301.6, U302.7
unnamed: U301.7, U302.6
unnamed: U301.8, U302.5
unnamed: U301.9, U302.4
unnamed: U301.10, U302.3
unnamed: U301.11, U302.2
USB_CTL0: J101.34, J202.31
USB_CTL1: J101.32, J202.29
USB_CTL2: J101.28, J202.27
USB_CTL3: J101.26, J202.25
USB_CTL4: J101.24, J202.23
USB_CTL5: J101.22, J202.21
USB_CTL6: J101.20, J202.19
USB_CTL7: J101.18, J202.17
USB_CTL8: J101.16, J202.15
USB_CTL9: J101.14, J202.13
USB_CTL10: J101.10, J202.11
USB_CTL11: J101.8, J202.9
USB_CTL12: J101.6, J202.7
USB_DATA0: J101.39, J202.38
USB_DATA1: J101.37, J202.36
USB_DATA2: J101.35, J202.34
USB_DATA3: J101.33, J202.32
USB_DATA4: J101.31, J202.30
USB_DATA5: J101.27, J202.28
USB_DATA6: J101.25, J202.26
USB_DATA7: J101.23, J202.24
USB_DATA8: J101.21, J202.22
USB_DATA9: J101.19, J202.20
USB_DATA10: J101.17, J202.18
USB_DATA11: J101.15, J202.16
USB_DATA12: J101.13, J202.14
USB_DATA13: J101.9, J202.12
USB_DATA14: J101.7, J202.10
USB_DATA15: J101.5, J202.8
USB_DATA16: J102.5, J201.38
USB_DATA17: J102.6, J201.36
USB_DATA18: J102.7, J201.34
USB_DATA19: J102.8, J201.32
USB_DATA20: J102.9, J201.30
USB_DATA21: J102.10, J201.28
USB_DATA22: J102.17, J201.26
USB_DATA23: J102.18, J201.24
USB_DATA24: J102.19, J201.22
USB_DATA25: J102.20, J201.20
USB_DATA26: J102.21, J201.18
USB_DATA27: J102.22, J201.16
USB_DATA28: J102.23, J201.12
USB_DATA29: J102.24, J201.10
USB_DATA30: J102.25, J201.8
USB_DATA31: J102.26, J201.6
USB_PCLK: J101.38, J202.35

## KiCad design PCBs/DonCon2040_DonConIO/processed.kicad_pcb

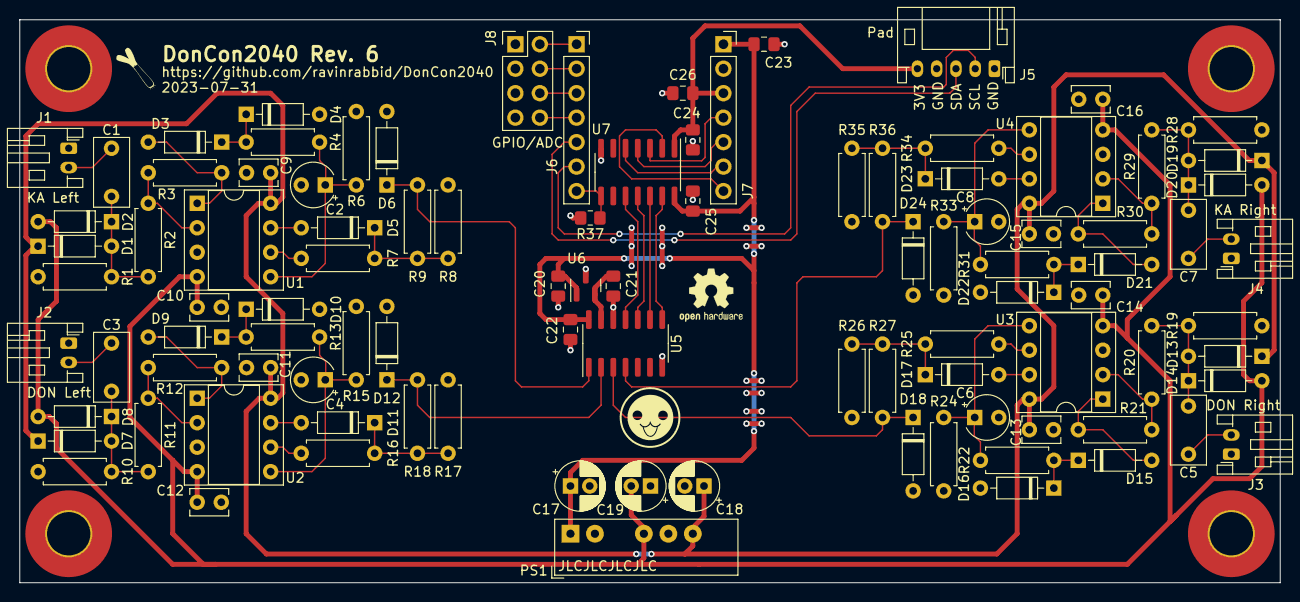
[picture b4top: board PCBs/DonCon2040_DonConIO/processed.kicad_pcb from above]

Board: 2 copper layers, 130.8 x 58.4 mm, 105 parts (0 on the bottom side), 61 nets.

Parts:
C1, C3, C5, C7: 1nF; C_Rect_L7.0mm_W3.5mm_P5.00mm
C2, C4, C6, C8: 0.47uF; CP_Radial_Tantal_D4.5mm_P2.50mm
C9, C10, C11, C12, C13, C14, C15, C16: 100nF; C_Disc_D3.8mm_W2.6mm_P2.50mm
C17: 4.7uF; CP_Radial_D5.0mm_P2.00mm
C18, C19: 1uF; CP_Radial_D5.0mm_P2.00mm
C20, C22, C24, C25: 0.1uF; C_0805_2012Metric_Pad1.18x1.45mm_HandSolder
C21, C23, C26: 10uF; C_0805_2012Metric_Pad1.18x1.45mm_HandSolder
D1, D2, D7, D8, D13, D14, D19, D20: 1SS133; D_DO-35_SOD27_P7.62mm_Horizontal
D3, D4, D9, D10, D15, D16, D21, D22: BAT43; D_DO-35_SOD27_P7.62mm_Horizontal
D5, D11, D17, D23: 1N4148; D_DO-35_SOD27_P7.62mm_Horizontal
D6: 4.1V; D_DO-35_SOD27_P7.62mm_Horizontal
D12, D18, D24: 4.3V; D_DO-35_SOD27_P7.62mm_Horizontal
H1, H2, H3, H4: MountingHole_Pad; MountingHole_4.5mm_Pad_TopOnly
J1: Ka Left; JST_PH_S2B-PH-K_1x02_P2.00mm_Horizontal
J2: Don Left; JST_PH_S2B-PH-K_1x02_P2.00mm_Horizontal
J3: Don Right; JST_PH_S2B-PH-K_1x02_P2.00mm_Horizontal
J4: Ka Right; JST_PH_S2B-PH-K_1x02_P2.00mm_Horizontal
J5: Pad; JST_PH_S5B-PH-K_1x05_P2.00mm_Horizontal
J6: MCU1; PinSocket_1x07_P2.54mm_Vertical
J7: MCU2; PinSocket_1x07_P2.54mm_Vertical
J8: GPIO/ADC; PinHeader_2x04_P2.54mm_Vertical
PS1: A0512S-1WR3; Converter_DCDC_XP_POWER-IAxxxxS_THT
R1, R10, R19, R28: 1M; R_Axial_DIN0207_L6.3mm_D2.5mm_P7.62mm_Horizontal
R2, R11, R20, R29: 4.7k; R_Axial_DIN0207_L6.3mm_D2.5mm_P7.62mm_Horizontal
R3, R12, R21, R30: 100k; R_Axial_DIN0207_L6.3mm_D2.5mm_P7.62mm_Horizontal
R4, R13, R22, R31: 100; R_Axial_DIN0207_L6.3mm_D2.5mm_P7.62mm_Horizontal
R6, R15, R24, R33: 5.1k; R_Axial_DIN0207_L6.3mm_D2.5mm_P7.62mm_Horizontal
R7, R16, R25, R34: 10k; R_Axial_DIN0207_L6.3mm_D2.5mm_P7.62mm_Horizontal
R8, R17, R26, R35: 1k; R_Axial_DIN0207_L6.3mm_D2.5mm_P7.62mm_Horizontal
R9, R18, R27, R36: 300; R_Axial_DIN0207_L6.3mm_D2.5mm_P7.62mm_Horizontal
R37: 10k; R_0805_2012Metric_Pad1.20x1.40mm_HandSolder
REF01: OSHW-Logo2_7.3x6mm_SilkScreen
REF02: Donchan-Logo_6.3mm_Silkscreen
U1, U2, U3, U4: TL072; DIP-8_W7.62mm_Socket
U5: MCP3204; SOIC-14_3.9x8.7mm_P1.27mm
U6: MCP1541-TT; SOT-23
U7: TXB0104D; SOIC-14_3.9x8.7mm_P1.27mm

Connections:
+3V3: C24.1, C26.2, J5.5, J7.3, U7.1 (VCCA)
+5V: C17.1, C20.2, C22.2, C23.2, C25.2, J7.1, PS1.1 (+Vin), U5.14 (Vdd), U6.1 (Vin), U7.14 (VCCB)
+12V: C9.1, C11.1, C13.1, C15.1, C18.1, D1.1 (K), D7.1 (K), D13.1 (K), D19.1 (K), PS1.6 (+Vout), U1.8 (V+), U2.8 (V+), U3.8 (V+), U4.8 (V+)
-12V: C10.1, C12.1, C14.1, C16.1, C19.2, D2.2 (A), D8.2 (A), D14.2 (A), D20.2 (A), PS1.4 (-Vout), U1.4 (V-), U2.4 (V-), U3.4 (V-), U4.4 (V-)
Don_Left_ADC: D12.1 (K), R18.1, U5.2 (CH1)
Don_Left_IN: C3.1, J2.2
Don_Right_ADC: D18.1 (K), R27.1, U5.3 (CH2)
Don_Right_IN: C5.1, J3.2
GND: C2.2, C4.2, C6.2, C8.2, C9.2, C10.2, C11.2, C12.2, C13.2, C14.2, C15.2, C16.2, C17.2, C18.2, C19.1, C20.1, C21.1, C22.1, C23.1, C24.2, C25.1, C26.1, D4.2 (A), D6.2 (A), D10.2 (A), D12.2 (A), D16.2 (A), D18.2 (A), D22.2 (A), D24.2 (A), H1.1, H2.1, H3.1, H4.1, J1.1, J2.1, J3.1, J4.1, J5.1, J5.4, J7.2, J8.1, J8.3, J8.5, J8.7, PS1.2 (-Vin), PS1.5 (0V), R1.2, R6.1, R8.1, R10.2, R15.1, R17.1, R19.2, R24.1, R26.1, R28.2, R33.1, R35.1, R37.2, U1.3 (+), U2.3 (+), U3.3 (+), U4.3 (+), U5.7 (DGND), U5.12 (AGND), U6.3 (Vss), U7.7 (GND)
Ka_Left_ADC: D6.1 (K), R9.1, U5.1 (CH0)
Ka_Left_IN: C1.1, J1.2
Ka_Right_ADC: D24.1 (K), R36.1, U5.4 (CH3)
Ka_Right_IN: C7.1, J4.2
unnamed: C1.2, D1.2 (A), D2.1 (K), R1.1, R2.2
unnamed: D3.2 (A), R3.2, U1.1
unnamed: D3.1 (K), D4.1 (K), R4.1
unnamed: D5.2 (A), U1.7
unnamed: D5.1 (K), R7.2, R8.2, R9.2
unnamed: C3.2, D7.2 (A), D8.1 (K), R10.1, R11.2
unnamed: D9.2 (A), R12.2, U2.1
unnamed: D9.1 (K), D10.1 (K), R13.1
unnamed: D11.2 (A), U2.7
unnamed: D11.1 (K), R16.2, R17.2, R18.2
unnamed: C5.2, D13.2 (A), D14.1 (K), R19.1, R20.2
unnamed: D15.2 (A), R21.2, U3.1
unnamed: D15.1 (K), D16.1 (K), R22.1
unnamed: D17.2 (A), U3.7
unnamed: D17.1 (K), R25.2, R26.2, R27.2
unnamed: C7.2, D19.2 (A), D20.1 (K), R28.1, R29.2
unnamed: D21.2 (A), R30.2, U4.1
unnamed: D21.1 (K), D22.1 (K), R31.1
unnamed: D23.2 (A), U4.7
unnamed: D23.1 (K), R34.2, R35.2, R36.2
unnamed: J6.1, J8.2
unnamed: J6.2, J8.4
unnamed: J6.3, J8.6
unnamed: J6.4, J8.8
unnamed: R2.1, R3.1, U1.2 (-)
unnamed: C2.1, R4.2, R6.2, U1.5 (+)
unnamed: R7.1, U1.6 (-)
unnamed: R11.1, R12.1, U2.2 (-)
unnamed: C4.1, R13.2, R15.2, U2.5 (+)
unnamed: R16.1, U2.6 (-)
unnamed: R20.1, R21.1, U3.2 (-)
unnamed: C6.1, R22.2, R24.2, U3.5 (+)
unnamed: R25.1, U3.6 (-)
unnamed: R29.1, R30.1, U4.2 (-)
unnamed: C8.1, R31.2, R33.2, U4.5 (+)
unnamed: R34.1, U4.6 (-)
unnamed: U5.11 (CLK), U7.10 (B4)
unnamed: U5.9 (Din), U7.12 (B2)
unnamed: U5.10 (Dout), U7.11 (B3)
unnamed: C21.2, U5.13 (Vref), U6.2 (Vout)
unnamed: U5.8 (~CS/SHDN), U7.13 (B1)
SCL: J5.2, J6.6
SDA: J5.3, J6.5
SPI MISO: J7.5, U7.4 (A3)
SPI MOSI: J7.4, U7.3 (A2)
SPI OE: J6.7, R37.1, U7.8 (OE)
SPI SCLK: J7.6, U7.5 (A4)
SPI nCS: J7.7, U7.2 (A1)

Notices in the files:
PCBs/DomesdayDuplicator_Domesday_Duplicator/processed.kicad_pcb:
(c)2018 Simon Inns
License: Attribution-ShareAlike 4.0 International (CC BY-SA 4.0)
